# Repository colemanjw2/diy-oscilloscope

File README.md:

#  DIY Cathode-Ray Tube Oscilloscope (2AP1A)

A fully discrete, high-voltage, electrostatic CRT oscilloscope built from first principles.

This project recreates the fundamental operation of early oscilloscopes using a vacuum tube, analog deflection amplifiers, and a high-voltage supply — with no digital processing, sampling, or abstraction.

It is based on the designs found here:

https://web.archive.org/web/20120718013731/http://mysite.du.edu/~etuttle/electron/elecindx.htm

And it is specifically this project:

https://web.archive.org/web/20120714102433/http://mysite.du.edu/~etuttle/electron/elect29.htm

Because the college that once hosted this site has decided to no longer do so, one must use WayBack Machine to view but I have also put the full webpage in a folder inside of this repo. 

---

## Overview

This oscilloscope is based around the **2AP1A cathode-ray tube**, a small electrostatic CRT that allows direct visualization of electrical signals through electron beam deflection.

Unlike modern oscilloscopes:
- No ADCs  
- No memory  
- No triggering system  

The display is a **real-time physical representation of voltage**.

---

##  System Architecture

The build consists of three primary subsystems:

### 1. CRT (Display Device)
- 2AP1A electrostatic CRT
- ~2" phosphor screen (P1 green, medium persistence)
- Electrostatic deflection plates (X/Y)

---

### 2. Deflection Amplifiers
- High-voltage analog amplifiers (~150–200 Vpp output)
- Drive the deflection plates directly
- Configurable for:
  - single-axis waveform display  
  - X-Y (Lissajous) mode  

---

### 3. High Voltage Power Supply
- ~700–800 V DC supply
- Low current (~1 mA total load)
- Resistive divider network for:
  - cathode bias  
  - grid control  
  - focusing  
  - anode voltages  

---

## CRT Operation (2AP1A)

Electron beam flow:

```

Cathode → Grid 1 → Anode 1 → Grid 2 → Anode 2 → Deflection Plates → Screen

```

### Functional Breakdown

| Element            | Function                          |
|------------------|----------------------------------|
| Cathode          | Thermionic electron emission     |
| Grid 1           | Intensity (beam current control) |
| Anode 1          | Pre-acceleration + beam shaping  |
| Grid 2           | Focus control (electrostatic lens) |
| Anode 2          | Main acceleration (~700–1000 V)  |
| Deflection Plates| Signal-driven beam steering      |
| Screen           | Phosphor emission                |

---

## Lissajous Mode (X-Y Operation)

When two signals are applied:

- X-axis → horizontal deflection  
- Y-axis → vertical deflection  

The CRT draws the relationship between them.

### Example

- X = 1000 Hz  
- Y = 999 Hz  

Result:
- Slowly rotating pattern  
- Drift rate = **1 Hz difference**

---

## ⚠️ Safety

This project involves **lethal high voltage**.

- 700–1000 V DC present  
- Capacitors retain charge after power-off  

### Recommendations:
- Use the one-hand rule when probing  
- Verify discharge before handling  
- Use properly rated components  
- Do not modify wiring while powered  

---

## Experiments Enabled

- Basic waveform visualization (no timebase)  
- X-Y plotting  
- Lissajous frequency comparison  
- Beam focusing and intensity control   

---

##  Build Notes

- Derived from classic oscilloscope circuits (ARRL-era designs)
- Uses modern components where practical
- CRT mounted with custom mechanical support
- Deflection plates AC-coupled for signal input

---

##  Project Video

https://youtu.be/sQTSOFO6ceU

---

##  Purpose

This project is not about performance.

It is about understanding:

- how electrons behave in electric fields  
- how analog systems represent signals  
- how early instrumentation worked  

---

## Key Idea

```

Voltage → electric field → force → motion → visible trace

```

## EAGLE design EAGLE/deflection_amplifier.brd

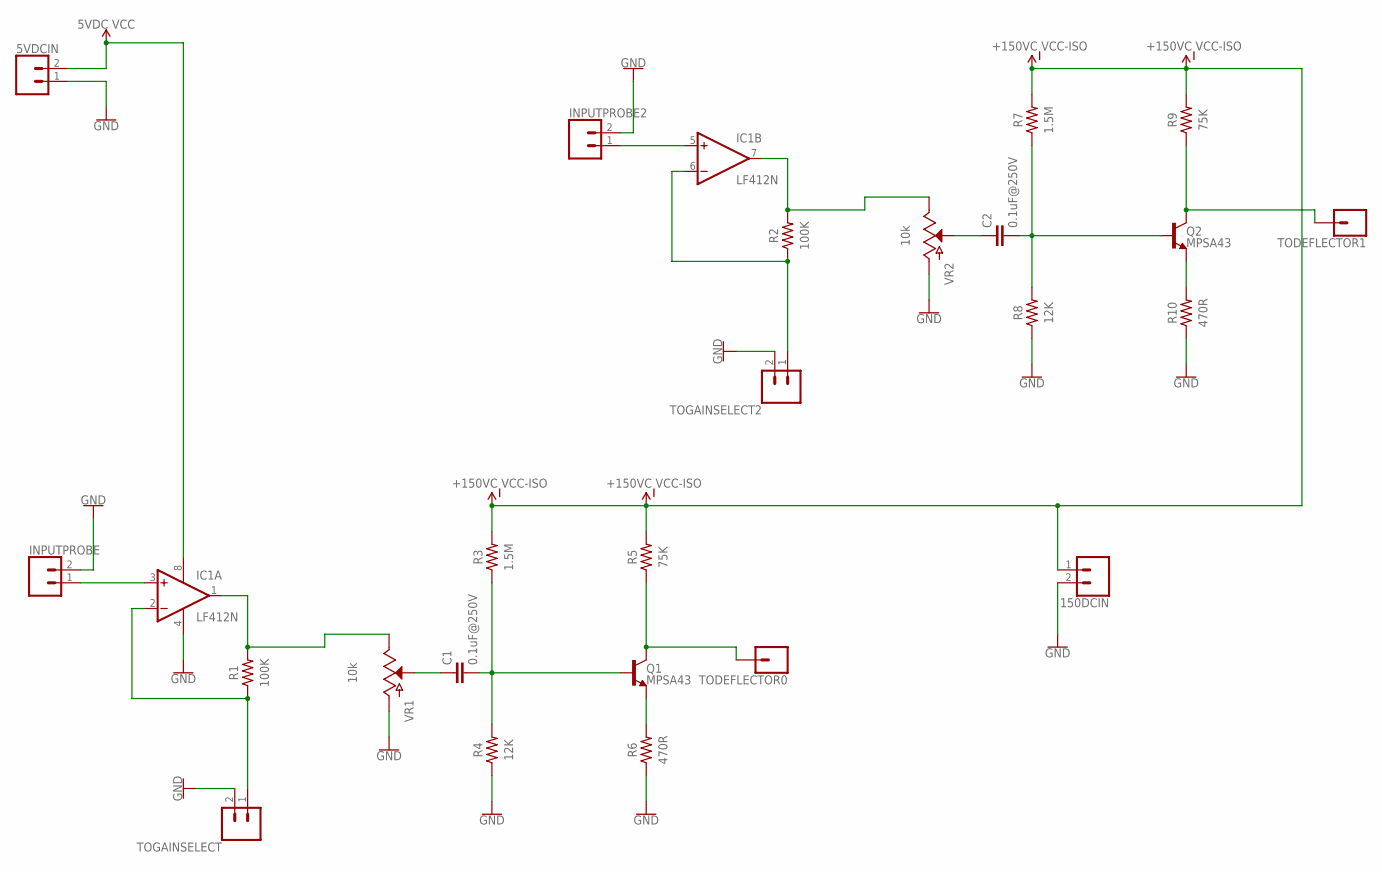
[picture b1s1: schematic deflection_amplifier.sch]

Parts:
5VDCIN, 150DCIN: CONN_02; 1X02
C1, C2: 0.1uF@250V; C15B8
IC1: LF412N; DIL08
INPUTPROBE, INPUTPROBE2: CONN_02; 1X02
Q1, Q2: MPSA43; TO-92
R1, R2: 100K; RESAD1176W63L850D250B
R3, R7: 1.5M; RESAD1176W63L850D250B
R4, R8: 12K; RESAD1176W63L850D250B
R5, R9: 75K; RESAD1176W63L850D250B
R6, R10: 470R; RESAD1176W63L850D250B
TODEFLECTOR0, TODEFLECTOR1: CONN_01; 1X01
TOGAINSELECT, TOGAINSELECT2: CONN_02; 1X02
VR1, VR2: 10k; POT-PTH-ALPS

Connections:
GND: 5VDCIN.1, 150DCIN.2, IC1.4 (V-), INPUTPROBE.2, INPUTPROBE2.2, R4.1, R6.1, R8.1, R10.1, TOGAINSELECT.2, TOGAINSELECT2.2, VR1.P$3 (A), VR2.P$3 (A)
unnamed: IC1.1 (OUT), R1.2, VR1.P$1 (E)
unnamed: IC1.2 (-IN), R1.1, TOGAINSELECT.1
unnamed: IC1.3 (+IN), INPUTPROBE.1
unnamed: C1.1, VR1.P$2 (S)
unnamed: C1.2, Q1.2 (B), R3.1, R4.2
unnamed: Q1.1 (E), R6.2
unnamed: Q1.3 (C), R5.1, TODEFLECTOR0.1
unnamed: IC1.7 (OUT), R2.2, VR2.P$1 (E)
unnamed: IC1.6 (-IN), R2.1, TOGAINSELECT2.1
unnamed: IC1.5 (+IN), INPUTPROBE2.1
unnamed: C2.1, VR2.P$2 (S)
unnamed: C2.2, Q2.2 (B), R7.1, R8.2
unnamed: Q2.1 (E), R10.2
unnamed: Q2.3 (C), R9.1, TODEFLECTOR1.1
VCC: 5VDCIN.2, IC1.8 (V+)
VCC-ISO: 150DCIN.1, R3.2, R5.2, R7.2, R9.2

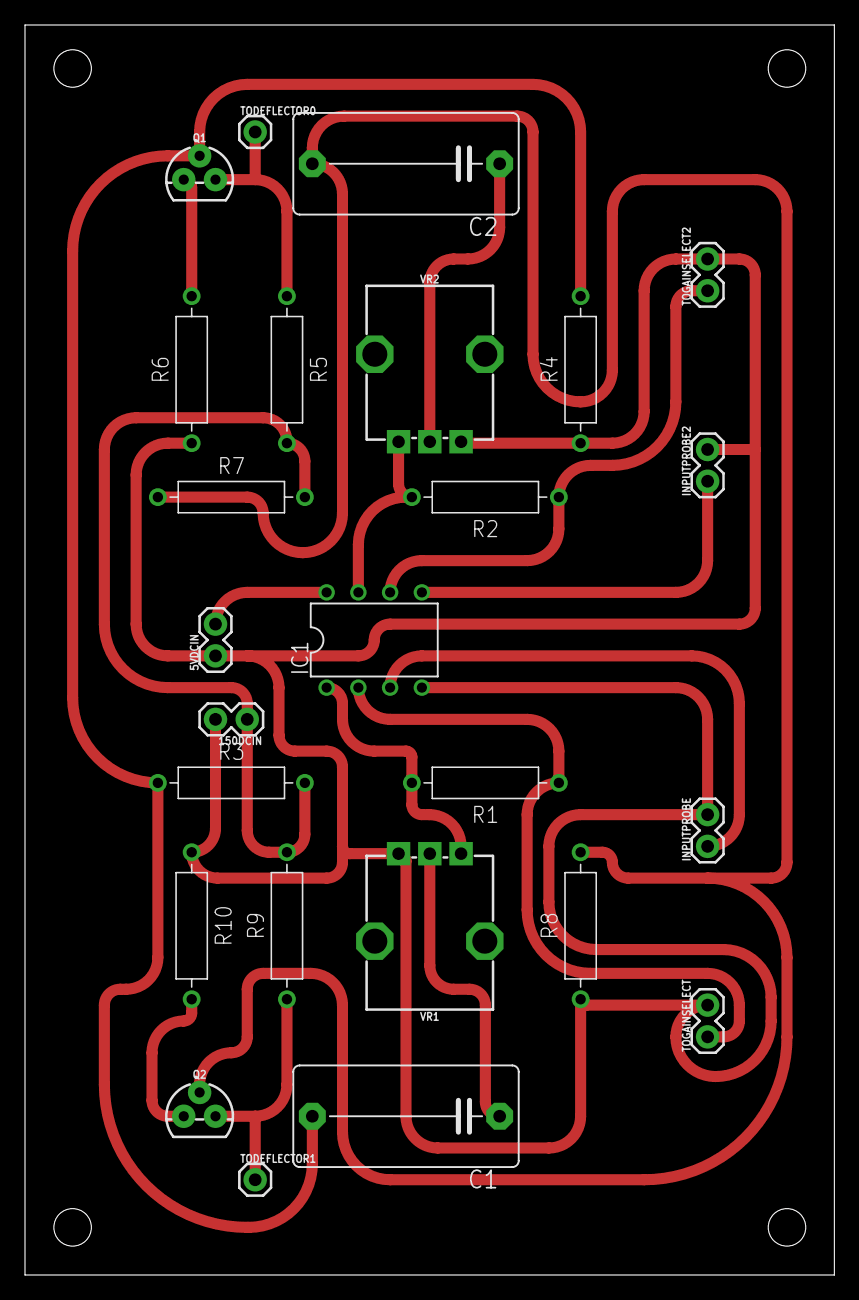
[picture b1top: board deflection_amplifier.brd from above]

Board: 2 copper layers, 64.8 x 100.0 mm, 25 parts (0 on the bottom side), 17 nets.

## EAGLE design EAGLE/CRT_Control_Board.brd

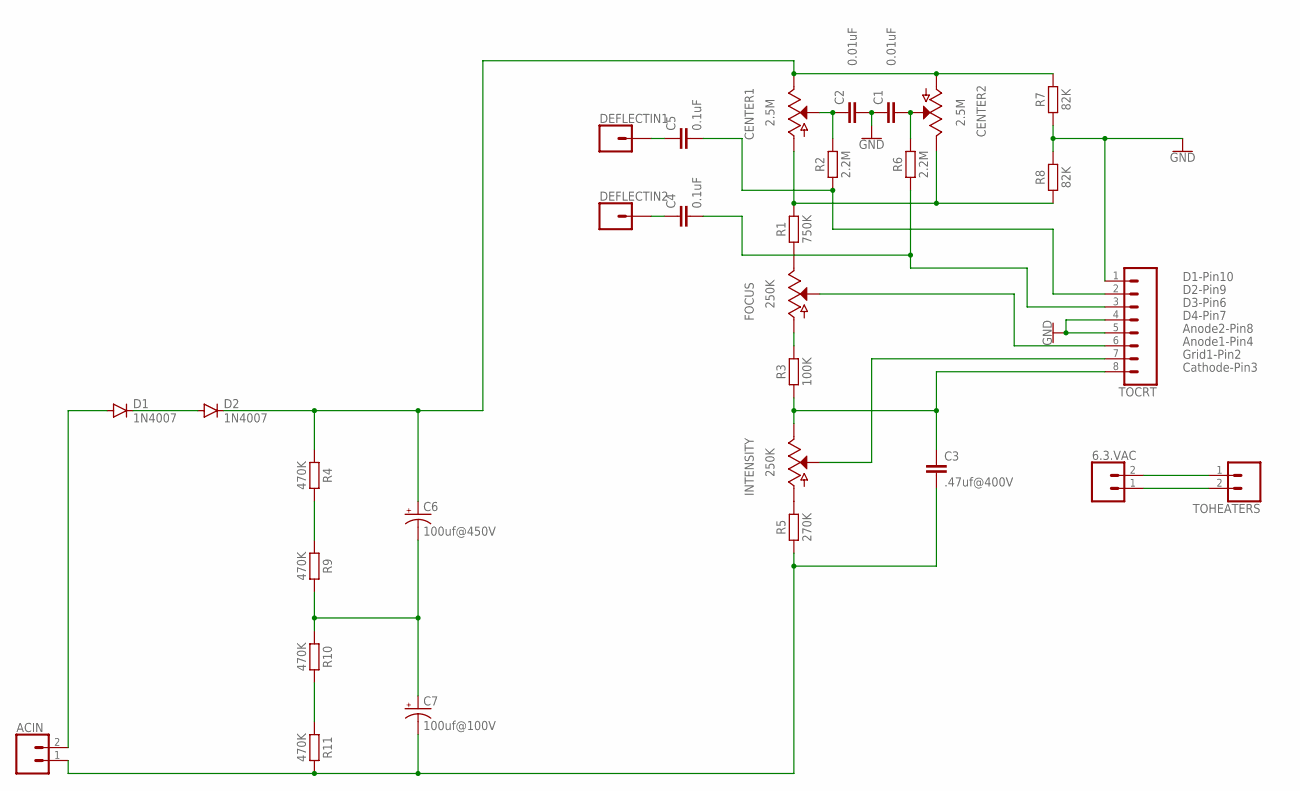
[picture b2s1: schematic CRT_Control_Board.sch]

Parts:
6.3.VAC: CONN_02; 1X02
ACIN: CONN_02; 1X02
C1, C2: 0.01uF; CAP-PTH-SMALL-KIT
C3: .47uf@400V; CAP-PTH-SMALL-KIT
C4, C5: 0.1uF; CAP-PTH-SMALL-KIT
C6: 100uf@450V; E5-6
C7: 100uf@100V; E5-6
CENTER1, CENTER2: 2.5M; POT-PTH-ALPS
D1, D2: 1N4007; DO41-10
DEFLECTIN1, DEFLECTIN2: CONN_01PTH_LONGPAD; 1X01_LONGPAD
FOCUS: 250K; POT-PTH-ALPS
INTENSITY: 250K; POT-PTH-ALPS
R1: 750K; RESAD1176W63L850D250B
R2, R6: 2.2M; RESAD1176W63L850D250B
R3: 100K; RESAD1176W63L850D250B
R4, R9, R10, R11: 470K; RESAD1176W63L850D250B
R5: 270K; RESAD1176W63L850D250B
R7, R8: 82K; RESAD1176W63L850D250B
TOCRT: CONN_08LONGPADS; 1X08_LONGPADS
TOHEATERS: CONN_02; 1X02

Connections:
GND: C1.1, C2.2, R7.1, R8.2, TOCRT.1, TOCRT.4, TOCRT.5
unnamed: C5.2, R2.1, TOCRT.2
unnamed: 6.3.VAC.2, TOHEATERS.1
unnamed: C6.+, CENTER1.P$1 (E), CENTER2.P$3 (A), D2.C, R4.1, R7.2
unnamed: INTENSITY.P$3 (A), R5.2
unnamed: C3.1, INTENSITY.P$1 (E), R3.1, TOCRT.8
unnamed: FOCUS.P$1 (E), R1.1
unnamed: FOCUS.P$3 (A), R3.2
unnamed: 6.3.VAC.1, TOHEATERS.2
unnamed: C4.2, R6.1, TOCRT.3
unnamed: C5.1, DEFLECTIN1.1
unnamed: C2.1, CENTER1.P$2 (S), R2.2
unnamed: C1.2, CENTER2.P$2 (S), R6.2
unnamed: FOCUS.P$2 (S), TOCRT.6
unnamed: INTENSITY.P$2 (S), TOCRT.7
unnamed: C4.1, DEFLECTIN2.1
unnamed: D1.C, D2.A
unnamed: ACIN.1, C3.2, C7.-, R5.1, R11.2
unnamed: R4.2, R9.1
unnamed: C6.-, C7.+, R9.2, R10.1
unnamed: R10.2, R11.1
unnamed: ACIN.2, D1.A
unnamed: CENTER1.P$3 (A), CENTER2.P$1 (E), R1.2, R8.1

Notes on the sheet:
D1-Pin10
D2-Pin9
D3-Pin6
D4-Pin7
Cathode-Pin3
Grid1-Pin2
Anode1-Pin4
Anode2-Pin8

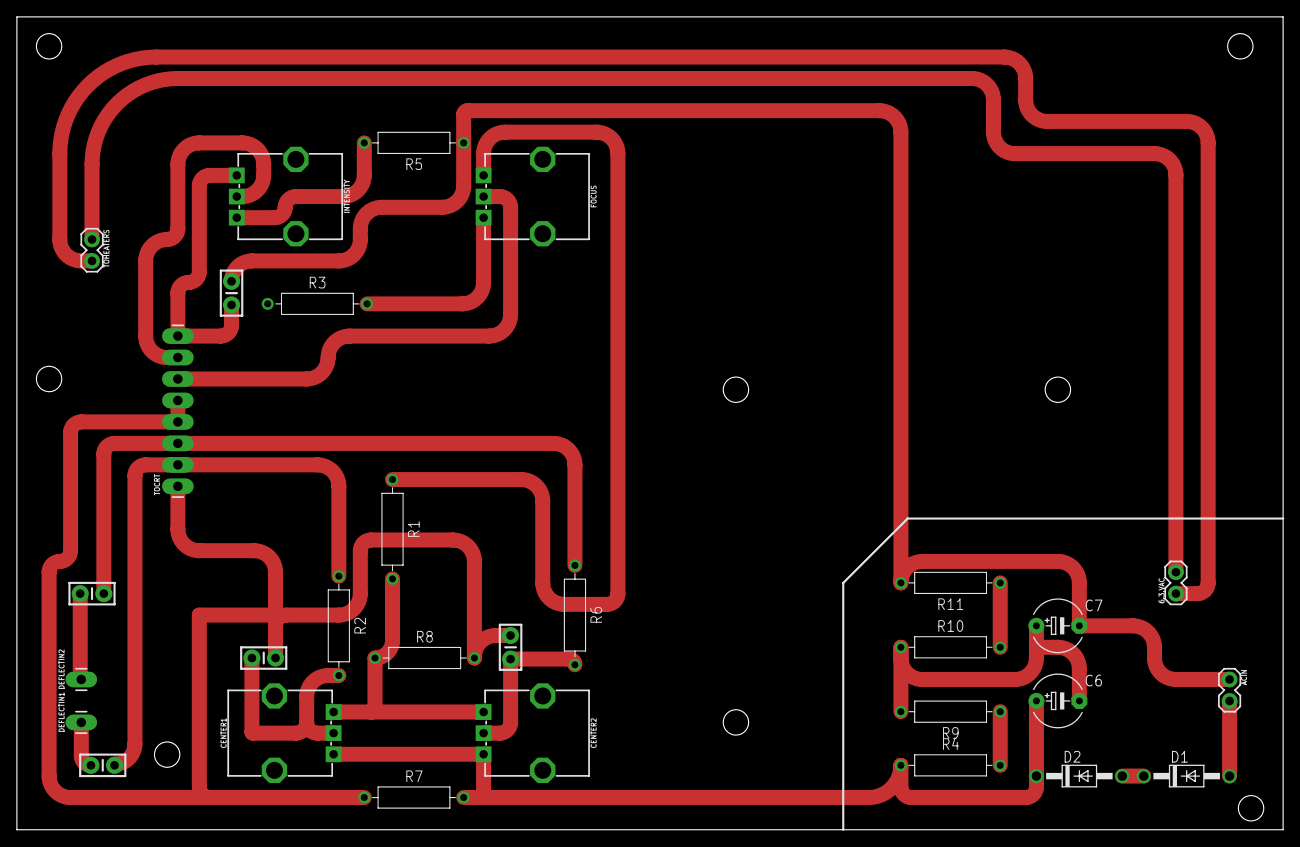
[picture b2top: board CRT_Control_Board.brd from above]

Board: 2 copper layers, 149.8 x 96.2 mm, 30 parts (0 on the bottom side), 23 nets.

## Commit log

2026-03-26 Revise README for DIY CRT Oscilloscope project
    Updated README to provide detailed project information and structure.
2026-03-26 Update README to focus on project description
    Removed introductory text and Markdown example.
2026-03-26 Refactor README section headings and content
    Updated section headings and removed redundant elements in the README.
2026-03-26 Fix formatting in README sections
2026-03-26 Fix formatting for Voltage Distribution section
2026-03-26 Update README with project references and details
    Added references to the original designs and project details.
2026-03-26 Clean up README by removing outdated sections
    Removed sections on deflection physics, voltage distribution, media, and future work from README.
2026-03-26 Add image of DIY CRT Oscilloscope to README
    Added an image to the README for visual reference.
2026-03-26 Add project video link to README

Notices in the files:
parts and their libraries:
SparkFun-Connectors: Licensing: Creative Commons ShareAlike 4.0 International - https://creativecommons.org/licenses/by-sa/4.0
